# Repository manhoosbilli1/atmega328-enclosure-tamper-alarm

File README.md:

# Alarming_AC_Enclosure

ATmega328-based AC enclosure tamper/intrusion alarm with PowerPath, voltage monitoring, and dual switching converters

## At a Glance

- **Status**: In progress
- **Board size**: 100 x 60 mm
- **Layers**: 2
- **Components**: 98
- **Key ICs**:
  - U1: 74LVC1G00
  - U2: ATmega328-A
  - U3: LM5158QRTERQ1
  - U4: TPS62933DRLR
  - U5: LTC4412ES6#TRPBF
  - U6: LTC2960CTS8-1#TRMPBF

## Schematic

Full PDF: [reports/schematic.pdf](reports/schematic.pdf)

## Component Roles

- **ATmega328-A** - main MCU; reads tamper switches, manages alarm state, drives outputs
- **LTC4412ES6** - low-loss ideal-diode / PowerPath controller; manages source switching between mains-derived rail and backup battery seamlessly
- **LTC2960CTS8-1** - precision voltage monitor / supervisor; trips the alarm if either supply rail dips out of spec
- **LM5158QRTERQ1** - automotive-grade boost converter (LM5158-Q1); steps up battery voltage to feed the alarm load when on backup
- **TPS62933PDRLR** - low-Iq buck converter for the MCU rail (long battery standby)
- **DMN10H220L** - N-channel MOSFET for high-side / load switching
- **FDC610PZ** - P-channel MOSFET (complementary side for OR-ing / load isolation)
- **B220** - Schottky diode for reverse / OR-ing logic
- **BZT52Bxx** - zener diode for clamp / reference
- **1TS005F-2500-5001** - tactile reset/test switch
- **74LVC1G00** - single 2-input NAND gate for combining tamper inputs / debounce logic
- **Crystal** for ATmega clock

> Designed as a self-powered enclosure tamper alarm: stays armed on AC, falls back to battery when AC is cut, alerts when either supply rail is out of spec.

## PCB

**Top copper**

**Bottom copper**

## Bill of Materials

| Refs | Value | Footprint | Qty | MPN | LCSC |
|------|-------|-----------|----:|-----|------|
| C1,C5,C18 | 100nF | Capacitor_SMD:C_0603_1608Metric | 3 |  |  |
| C2,C3,C7,C17,C22,C25 | 100nF | Capacitor_SMD:C_0402_1005Metric | 6 |  |  |
| C4,C13,C14 | 4.7uF | Capacitor_SMD:C_0603_1608Metric | 3 |  |  |
| C6 | 22nF | Capacitor_SMD:C_0402_1005Metric | 1 |  |  |
| C8 | 10nF | Capacitor_SMD:C_0402_1005Metric | 1 |  |  |
| C9 | 1uF | Capacitor_SMD:C_0402_1005Metric | 1 |  |  |
| C10 | 100pF | Capacitor_SMD:C_0402_1005Metric | 1 |  |  |
| C11,C12 | 22pF | Capacitor_SMD:C_0402_1005Metric | 2 |  |  |
| C15,C16 | 10uF/50V | Capacitor_SMD:C_0805_2012Metric | 2 |  |  |
| C19,C20,C26 | 100uF/35V | Capacitor_SMD:CP_Elec_6.3x7.7 | 3 |  |  |
| C21 | 33nF | Capacitor_SMD:C_0402_1005Metric | 1 |  |  |
| C23,C24 | 22uF/35v | Capacitor_SMD:C_0805_2012Metric | 2 |  |  |
| D1 | B220 | Diode_SMD:D_SMB | 1 |  |  |
| D2 | BZT52B2V4 | Diode_SMD:D_SOD-123F | 1 |  |  |
| D3 | RED | LED_SMD:LED_0603_1608Metric | 1 |  |  |
| J1 | AVR-ISP-6 | Connector_PinSocket_2.54mm:PinSocket_2x03_P2.54mm_Vertical | 1 |  |  |
| J2 | Conn_01x04 | TerminalBlock_Phoenix:TerminalBlock_Phoenix_PT-1,5-4-3.5-H_1x04_P3.50mm_Horizontal | 1 |  |  |
| J3 | Conn_01x03 | TerminalBlock_Phoenix:TerminalBlock_Phoenix_PT-1,5-3-3.5-H_1x03_P3.50mm_Horizontal | 1 |  |  |
| J4 | BATTERY IN | TerminalBlock_Phoenix:TerminalBlock_Phoenix_PT-1,5-2-3.5-H_1x02_P3.50mm_Horizontal | 1 |  |  |
| J5 | WALL IN | TerminalBlock_Phoenix:TerminalBlock_Phoenix_PT-1,5-2-3.5-H_1x02_P3.50mm_Horizontal | 1 |  |  |
| L1 | 1.5uH | Inductor_SMD:L_Sunlord_MWSA0603S | 1 |  |  |
| L2 | 6.8uH | Inductor_SMD:L_TDK_SLF10165 | 1 |  |  |
| Q1-Q3 | DMN10H220L | Package_TO_SOT_SMD:SOT-23 | 3 |  |  |
| Q4,Q6 | FDC610PZ | FDC610PZ:SOT-23-6_L2.9-W1.6-P0.95-LS2.8-BR | 2 |  |  |
| Q5,Q7 | SI4435DY | SI4435DY:SOP-8_L4.9-W3.9-P1.27-LS6.0-BL | 2 |  |  |
| R1,R10-R14,R17 | 10K | Resistor_SMD:R_0603_1608Metric | 7 |  |  |
| R2 | 9.09K | Resistor_SMD:R_0402_1005Metric | 1 |  |  |
| R3 | 2.61K | Resistor_SMD:R_0402_1005Metric | 1 |  |  |
| R4,R20 | 1M | Resistor_SMD:R_0603_1608Metric | 2 |  |  |
| R5 | 49.9K 1% | Resistor_SMD:R_0402_1005Metric | 1 |  |  |
| R6 | 2.15K 1% | Resistor_SMD:R_0402_1005Metric | 1 |  |  |
| R7-R9 | 100R | Resistor_SMD:R_0603_1608Metric | 3 |  |  |
| R15 | 3M | Resistor_SMD:R_0603_1608Metric | 1 |  |  |
| R16 | 82K | Resistor_SMD:R_0603_1608Metric | 1 |  |  |
| R18 | 10.2K 1% | Resistor_SMD:R_0402_1005Metric | 1 |  |  |
| R19 | 53.6k 1% | Resistor_SMD:R_0402_1005Metric | 1 |  |  |
| R21,R22,R27 | 100K | Resistor_SMD:R_0603_1608Metric | 3 |  |  |
| R23 | 49.9R 1% | Resistor_SMD:R_0402_1005Metric | 1 |  |  |
| R24 | 4.7K | Resistor_SMD:R_0603_1608Metric | 1 |  |  |
| R25 | 4.3K | Resistor_SMD:R_0603_1608Metric | 1 |  |  |
| R26 | 510K | Resistor_SMD:R_0603_1608Metric | 1 |  |  |
| R28 | 5.6M | Resistor_SMD:R_0603_1608Metric | 1 |  |  |
| RV1,RV2 | 10K | Potentiometer_SMD:Potentiometer_Bourns_3314J_Vertical | 2 |  |  |
| SW1 | 1TS005F-2500-5001 | 1TS005F-2500-5001:SW-SMD_4P-L6.0-W6.0-P4.50-LS9.0-H2.5 | 1 |  |  |
| SW2,SW3 | SW_Push | TerminalBlock_Phoenix:TerminalBlock_Phoenix_PT-1,5-2-3.5-H_1x02_P3.50mm_Horizontal | 2 |  |  |
| TP1,TP2 | TestPoint | TestPoint:TestPoint_Pad_D1.5mm | 2 |  |  |
| U1 | 74LVC1G00 | Package_TO_SOT_SMD:SOT-23-5 | 1 |  |  |
| U2 | ATmega328-A | Package_QFP:TQFP-32_7x7mm_P0.8mm | 1 |  |  |
| U3 | LM5158QRTERQ1 | Package_DFN_QFN:WQFN-16-1EP_3x3mm_P0.5mm_EP1.68x1.68mm | 1 |  |  |
| U4 | TPS62933DRLR | Package_TO_SOT_SMD:SOT-583-8 | 1 |  |  |
| U5 | LTC4412ES6#TRPBF | LTC4412ES6#TRPBF:TSOT-23-6_L2.9-W1.6-P0.95-LS2.8-BR | 1 |  |  |
| U6 | LTC2960CTS8-1#TRMPBF | LTC2960CTS8-1#TRMPBF:TSOT-23-8_L2.9-W1.6-P0.65-LS2.8-BL | 1 |  |  |
| Y1 | 16MHZ | Crystal:Crystal_SMD_5032-2Pin_5.0x3.2mm | 1 |  |  |

_53 of 53 line items don't have an LCSC code in the schematic - search [LCSC](https://www.lcsc.com/) or [JLC parts search](https://jlcsearch.tscircuit.com/) by MPN or footprint when sourcing._

## Files

- `Alarming_AC_Enclosure.kicad_pro` - KiCad project
- `Alarming_AC_Enclosure.kicad_sch` - schematic source
- `Alarming_AC_Enclosure.kicad_pcb` - PCB layout source
- `reports/schematic.pdf` - full schematic (printable)
- `reports/bom.csv` - bill of materials
- `reports/pcb-top.svg`, `reports/pcb-bottom.svg` - copper artwork
- `reports/board-stats.json` - KiCad-generated board statistics

---

_Renders and metadata auto-generated by `Backup-KiCadProject.ps1` using KiCad 10.0._

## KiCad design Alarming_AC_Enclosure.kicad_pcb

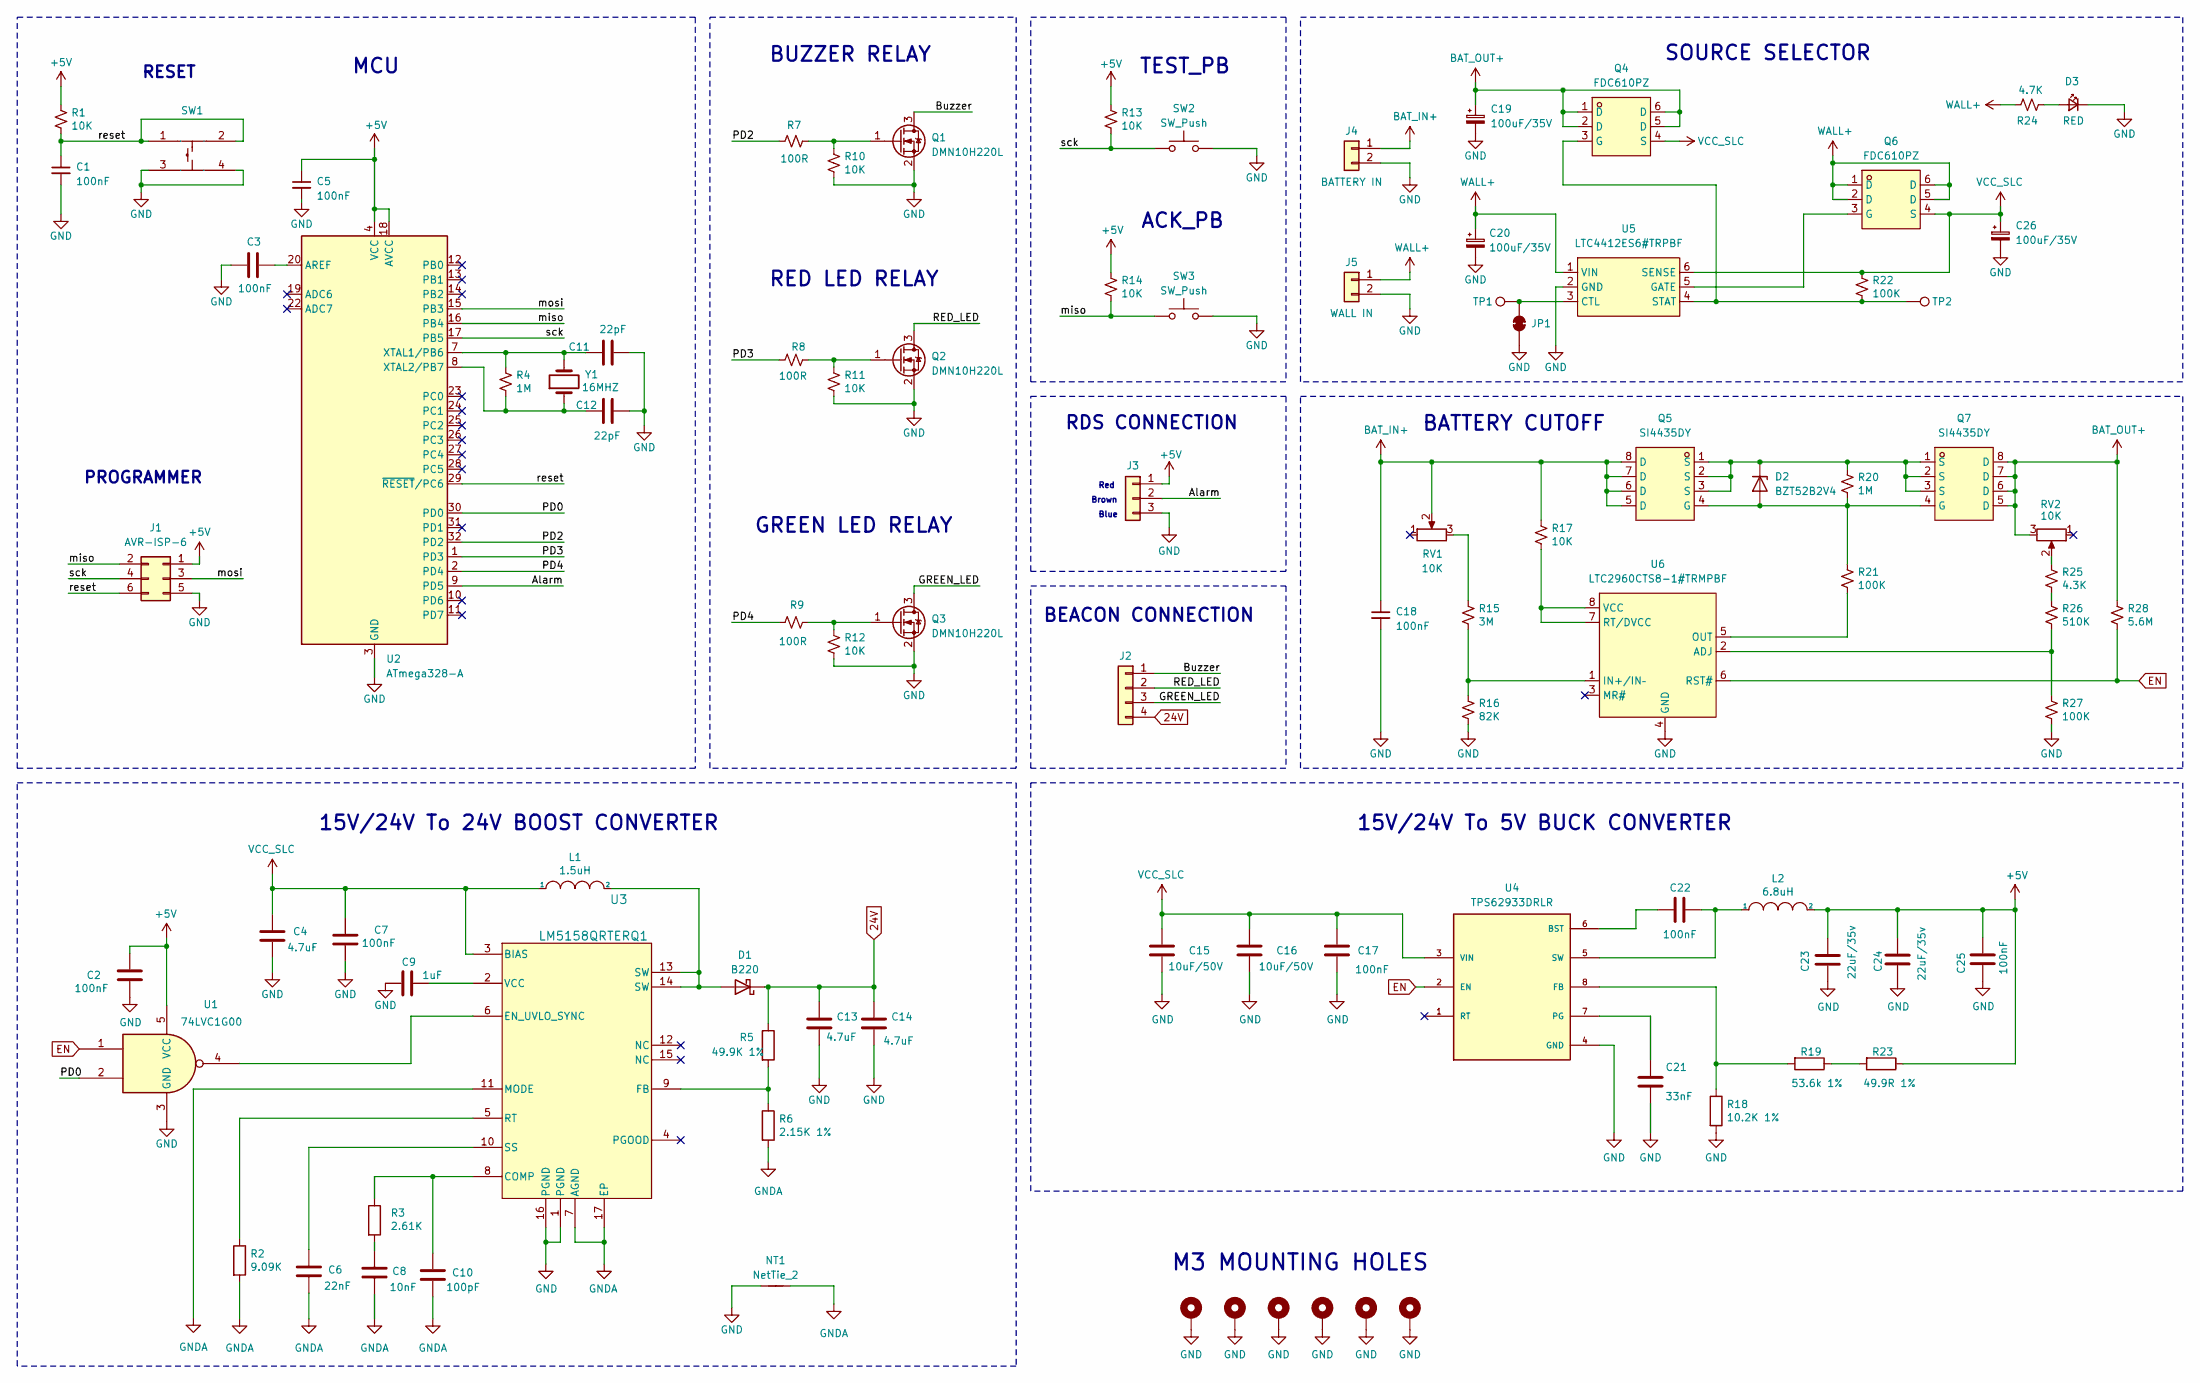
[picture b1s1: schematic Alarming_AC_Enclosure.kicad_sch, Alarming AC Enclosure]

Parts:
C1, C5, C18: 100nF; C_0603_1608Metric; JLCPCB Part # C14663
C2, C3, C7, C17, C22, C25: 100nF; C_0402_1005Metric; JLCPCB Part # C307331
C4, C13, C14: 4.7uF; C_0603_1608Metric; JLCPCB Part # C69335
C6: 22nF; C_0402_1005Metric; JLCPCB Part # C1532
C8: 10nF; C_0402_1005Metric; JLCPCB Part # C15195
C9: 1uF; C_0402_1005Metric; JLCPCB Part # C52923
C10: 100pF; C_0402_1005Metric; JLCPCB Part # C1546
C11, C12: 22pF; C_0402_1005Metric; JLCPCB Part # C1555
C15, C16: 10uF/50V; C_0805_2012Metric; JLCPCB Part # C440198
C19, C20, C26: 100uF/35V; CP_Elec_6.3x7.7; JLCPCB Part # C3339
C21: 33nF; C_0402_1005Metric; JLCPCB Part # C106862
C23, C24: 22uF/35v; C_0805_2012Metric; JLCPCB Part # C338080
D1: B220; D_SMB; JLCPCB Part # C110480
D2: BZT52B2V4; D_SOD-123F; JLCPCB Part # C3019930
D3: RED; LED_0603_1608Metric; JLCPCB Part # C2286
H1, H2, H3, H4, H5, H6: MountingHole; MountingHole_3.2mm_M3_DIN965_Pad
J1: AVR-ISP-6; PinSocket_2x03_P2.54mm_Vertical; JLCPCB Part # C7501274
J2: Conn_01x04; TerminalBlock_Phoenix_PT-1,5-4-3.5-H_1x04_P3.50mm_Horizontal; JLCPCB Part # C2757925
J3: Conn_01x03; TerminalBlock_Phoenix_PT-1,5-3-3.5-H_1x03_P3.50mm_Horizontal; JLCPCB Part # C466971
J4: BATTERY IN; TerminalBlock_Phoenix_PT-1,5-2-3.5-H_1x02_P3.50mm_Horizontal; JLCPCB Part # C415432
J5: WALL IN; TerminalBlock_Phoenix_PT-1,5-2-3.5-H_1x02_P3.50mm_Horizontal; JLCPCB Part # C415432
JP1: SolderJumper_2_Bridged; SolderJumper-2_P1.3mm_Bridged_RoundedPad1.0x1.5mm
L1: 1.5uH; L_Sunlord_MWSA0603S; JLCPCB Part # C167217
L2: 6.8uH; L_TDK_SLF10165; JLCPCB Part # C138669
NT1: NetTie_2; NetTie-2_SMD_Pad2.0mm
Q1, Q2, Q3: DMN10H220L; SOT-23; JLCPCB Part # C5122013
Q4, Q6: FDC610PZ; SOT-23-6_L2.9-W1.6-P0.95-LS2.8-BR; JLCPCB Part # C241761
Q5, Q7: SI4435DY; SOP-8_L4.9-W3.9-P1.27-LS6.0-BL; JLCPCB Part # C4355022
R1, R10, R11, R12, R13, R14, R17: 10K; R_0603_1608Metric; JLCPCB Part # C25804
R2: 9.09K; R_0402_1005Metric; JLCPCB Part # C11549
R3: 2.61K; R_0402_1005Metric; JLCPCB Part # C34906
R4, R20: 1M; R_0603_1608Metric; JLCPCB Part # C22935
R5: 49.9K 1%; R_0402_1005Metric; JLCPCB Part # C25897
R6: 2.15K 1%; R_0402_1005Metric; JLCPCB Part # C25878
R7, R8, R9: 100R; R_0603_1608Metric; JLCPCB Part # C22775
R15: 3M; R_0603_1608Metric; JLCPCB Part # C23156
R16: 82K; R_0603_1608Metric; JLCPCB Part # C23254
R18: 10.2K 1%; R_0402_1005Metric; JLCPCB Part # C11660
R19: 53.6k 1%; R_0402_1005Metric; JLCPCB Part # C53398
R21, R22, R27: 100K; R_0603_1608Metric; JLCPCB Part # C25803
R23: 49.9R 1%; R_0402_1005Metric; JLCPCB Part # C25120
R24: 4.7K; R_0603_1608Metric; JLCPCB Part # C23162
R25: 4.3K; R_0603_1608Metric; JLCPCB Part # C23159
R26: 510K; R_0603_1608Metric; JLCPCB Part # C23192
R28: 5.6M; R_0603_1608Metric; JLCPCB Part # C23190
RV1, RV2: 10K; Potentiometer_Bourns_3314J_Vertical; JLCPCB Part # C36376
SW1: 1TS005F-2500-5001; SW-SMD_4P-L6.0-W6.0-P4.50-LS9.0-H2.5; JLCPCB Part # C255812
SW2, SW3: SW_Push; TerminalBlock_Phoenix_PT-1,5-2-3.5-H_1x02_P3.50mm_Horizontal; JLCPCB Part # C415432
TP1, TP2: TestPoint; TestPoint_Pad_D1.5mm
U1: 74LVC1G00; SOT-23-5; JLCPCB Part # C434066
U2: ATmega328-A; TQFP-32_7x7mm_P0.8mm; JLCPCB Part # C14877
U3: LM5158QRTERQ1; WQFN-16-1EP_3x3mm_P0.5mm_EP1.68x1.68mm; JLCPCB Part # C3188431
U4: TPS62933DRLR; SOT-583-8; JLCPCB Part # C3200405
U5: LTC4412ES6#TRPBF; TSOT-23-6_L2.9-W1.6-P0.95-LS2.8-BR; JLCPCB Part # C514442
U6: LTC2960CTS8-1#TRMPBF; TSOT-23-8_L2.9-W1.6-P0.65-LS2.8-BL; JLCPCB Part # C683822
Y1: 16MHZ; Crystal_SMD_5032-2Pin_5.0x3.2mm; JLCPCB Part # C251590

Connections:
24V: C13.1, C14.1, D1.1 (K), J2.4, R5.1; also elsewhere on the board
+5V: C2.2, C5.1, C23.1, C24.1, C25.2, J1.1, J3.1, L2.2, R1.1, R13.1, R14.1, R23.1, U1.5 (VCC), U2.4 (VCC), U2.6 (VCC), U2.18 (AVCC); also elsewhere on the board
/Alarm: J3.2, U2.9 (PD5)
/Buzzer: J2.1, Q1.3 (D)
/GREEN_LED: J2.3, Q3.3 (D)
/PD0: U1.2, U2.30 (PD0)
/PD2: R7.1, U2.32 (PD2)
/PD3: R8.1, U2.1 (PD3)
/PD4: R9.1, U2.2 (PD4)
/RED_LED: J2.2, Q2.3 (D)
/miso: J1.2, R14.2, SW3.1, U2.16 (PB4)
/mosi: J1.3, U2.15 (PB3)
/reset: C1.1, J1.6, R1.2, SW1.1, SW1.2, U2.29 (~RESET/PC6)
/sck: J1.4, R13.2, SW2.1, U2.17 (PB5)
BAT_IN+: C18.1, J4.1, Q5.5 (D), Q5.6 (D), Q5.7 (D), Q5.8 (D), R17.1, RV1.2
BAT_OUT+: C19.1, Q4.1 (D), Q4.2 (D), Q4.5 (D), Q4.6 (D), Q7.5 (D), Q7.6 (D), Q7.7 (D), Q7.8 (D), R28.1, RV2.3
EN: R28.2, U1.1, U4.2 (EN), U6.6 (RST#)
GND: C1.2, C2.1, C3.2, C4.2, C5.2, C7.1, C9.1, C11.2, C12.2, C13.2, C14.2, C15.2, C16.2, C17.1, C18.2, C19.2, C20.2, C21.2, C23.2, C24.2, C25.1, C26.2, D3.1 (K), H1.1, H2.1, H3.1, H4.1, H5.1, H6.1, J1.5, J3.3, J4.2, J5.2, JP1.1 (A), NT1.1, Q1.2 (S), Q2.2 (S), Q3.2 (S), R10.2, R11.2, R12.2, R16.2, R18.2, R27.2, SW1.3, SW1.4, SW2.2, SW3.2, U1.3 (GND), U2.3 (GND), U2.5 (GND), U2.21 (GND), U3.1 (PGND), U3.16 (PGND), U4.4 (GND), U5.2 (GND), U6.4 (GND); also elsewhere on the board
GNDA: C6.2, C8.2, C10.2, NT1.2, R2.2, R6.2, U3.7 (AGND), U3.11 (MODE), U3.17 (EP)
unnamed: C8.1, R3.2
unnamed: D1.2 (A), L1.2, U3.13 (SW), U3.14 (SW)
unnamed: D2.2 (A), Q5.4 (G), Q7.4 (G), R20.2, R21.1
unnamed: D2.1 (K), Q5.1 (S), Q5.2 (S), Q5.3 (S), Q7.1 (S), Q7.2 (S), Q7.3 (S), R20.1
unnamed: D3.2 (A), R24.2
unnamed: JP1.2 (B), TP1.1, U5.3 (CTL)
unnamed: Q1.1 (G), R7.2, R10.1
unnamed: Q2.1 (G), R8.2, R11.1
unnamed: Q3.1 (G), R9.2, R12.1
unnamed: Q4.3 (G), R22.2, TP2.1, U5.4 (STAT)
unnamed: Q6.3 (G), U5.5 (GATE)
unnamed: R15.1, RV1.3
unnamed: R19.1, R23.2
unnamed: R25.1, RV2.2
unnamed: R25.2, R26.1
unnamed: C3.1, U2.20 (AREF)
unnamed: C11.1, R4.1, U2.7 (XTAL1/PB6), Y1.2
unnamed: C12.1, R4.2, U2.8 (XTAL2/PB7), Y1.1
unnamed: C10.1, R3.1, U3.8 (COMP)
unnamed: U1.4, U3.6 (EN_UVLO_SYNC)
unnamed: R5.2, R6.1, U3.9 (FB)
unnamed: R2.1, U3.5 (RT)
unnamed: C6.1, U3.10 (SS)
unnamed: C9.2, U3.2 (VCC)
unnamed: C22.1, U4.6 (BST)
unnamed: R18.1, R19.2, U4.8 (FB)
unnamed: C21.1, U4.7 (PG)
unnamed: C22.2, L2.1, U4.5 (SW)
unnamed: R26.2, R27.1, U6.2 (ADJ)
unnamed: R15.2, R16.1, U6.1 (IN+/IN–)
unnamed: R21.2, U6.5 (OUT)
unnamed: R17.2, U6.7 (RT/DVCC), U6.8 (VCC)
VCC_SLC: C4.1, C7.2, C15.1, C16.1, C17.2, C26.1, L1.1, Q4.4 (S), Q6.4 (S), R22.1, U3.3 (BIAS), U4.3 (VIN), U5.6 (SENSE)
WALL+: C20.1, J5.1, Q6.1 (D), Q6.2 (D), Q6.5 (D), Q6.6 (D), R24.1, U5.1 (VIN)

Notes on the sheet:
Red
Blue
15V/24V To 24V BOOST CONVERTER
RED LED RELAY
TEST_PB
15V/24V To 5V BUCK CONVERTER
RDS CONNECTION
ACK_PB
Brown
RESET
BATTERY CUTOFF
MCU
SOURCE SELECTOR
M3 MOUNTING HOLES
BEACON CONNECTION
PROGRAMMER
BUZZER RELAY
GREEN LED RELAY

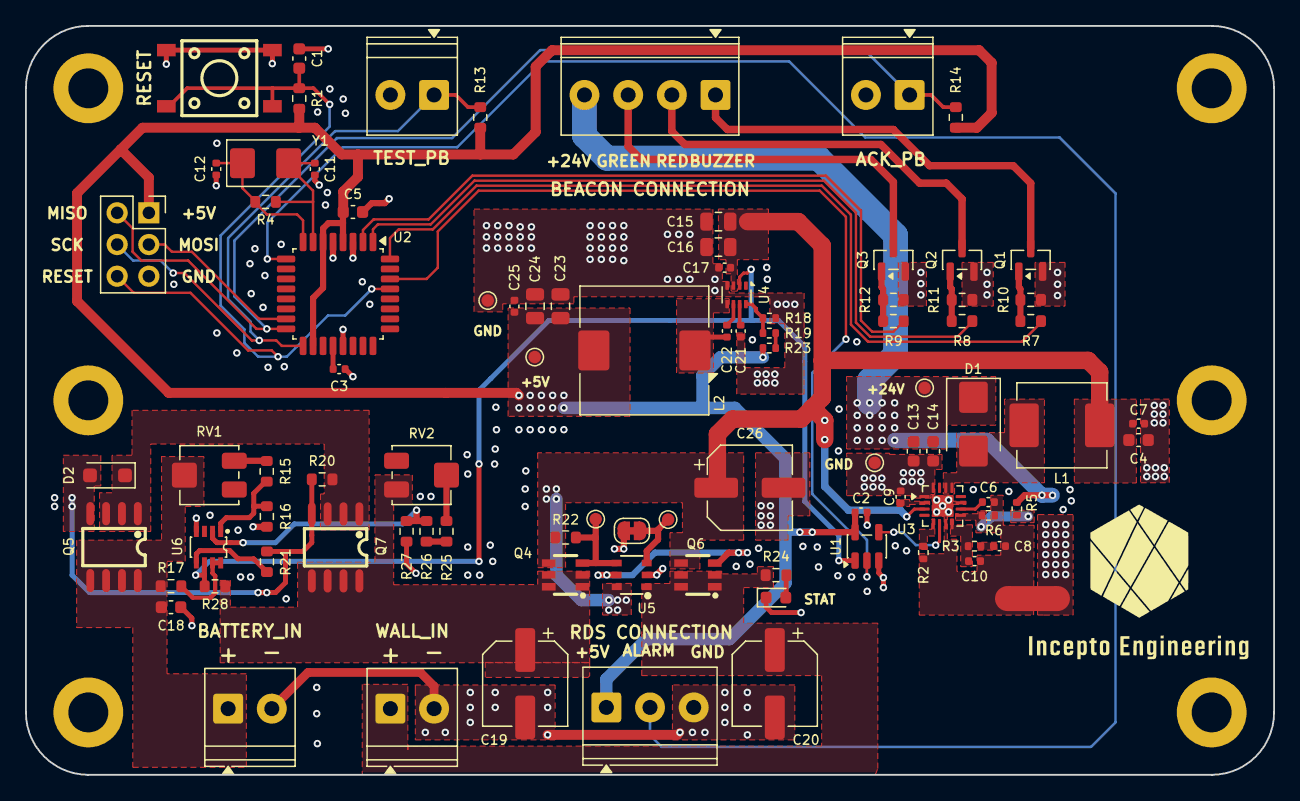
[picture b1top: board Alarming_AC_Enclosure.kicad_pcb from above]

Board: 2 copper layers, 100.0 x 60.0 mm, 97 parts (0 on the bottom side), 53 nets.

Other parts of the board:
TP3, TP4, TP5, TP6: TestPoint; TestPoint_Pad_D1.0mm

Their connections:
24V: TP3.1; also elsewhere on the board
+5V: TP5.1; also elsewhere on the board
GND: TP4.1, TP6.1; also elsewhere on the board

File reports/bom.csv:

"Refs","Value","Footprint","Qty","Description","Mfr","MPN","LCSC"
"C1,C5,C18","100nF","Capacitor_SMD:C_0603_1608Metric","3","","","",""
"C2,C3,C7,C17,C22,C25","100nF","Capacitor_SMD:C_0402_1005Metric","6","","","",""
"C4,C13,C14","4.7uF","Capacitor_SMD:C_0603_1608Metric","3","","","",""
"C6","22nF","Capacitor_SMD:C_0402_1005Metric","1","","","",""
"C8","10nF","Capacitor_SMD:C_0402_1005Metric","1","","","",""
"C9","1uF","Capacitor_SMD:C_0402_1005Metric","1","","","",""
"C10","100pF","Capacitor_SMD:C_0402_1005Metric","1","","","",""
"C11,C12","22pF","Capacitor_SMD:C_0402_1005Metric","2","","","",""
"C15,C16","10uF/50V","Capacitor_SMD:C_0805_2012Metric","2","","","",""
"C19,C20,C26","100uF/35V","Capacitor_SMD:CP_Elec_6.3x7.7","3","-55℃~+105℃ 100uF 2000hrs@105℃ 35V 6.3mm 7.7mm ±20% SMD,D6.3xL7.7mm Aluminum Electrolytic Capacitors - SMD ROHS","","",""
"C21","33nF","Capacitor_SMD:C_0402_1005Metric","1","","","",""
"C23,C24","22uF/35v","Capacitor_SMD:C_0805_2012Metric","2","","","",""
"D1","B220","Diode_SMD:D_SMB","1","","","",""
"D2","BZT52B2V4","Diode_SMD:D_SOD-123F","1","500mW Zener Diode, SOD-123F","","",""
"D3","RED","LED_SMD:LED_0603_1608Metric","1","-40℃~+85℃ 120° 2.4V 20mA 300mcd 40mW 615nm~630nm 645nm Red Water Clear 0603 LED Indication - Discrete ROHS","","",""
"J1","AVR-ISP-6","Connector_PinSocket_2.54mm:PinSocket_2x03_P2.54mm_Vertical","1","Generic connector, double row, 02x03, odd/even pin numbering scheme (row 1 odd numbers, row 2 even numbers), script generated (kicad-library-utils/schlib/autogen/connector/)","","",""
"J2","Conn_01x04","TerminalBlock_Phoenix:TerminalBlock_Phoenix_PT-1,5-4-3.5-H_1x04_P3.50mm_Horizontal","1","","","",""
"J3","Conn_01x03","TerminalBlock_Phoenix:TerminalBlock_Phoenix_PT-1,5-3-3.5-H_1x03_P3.50mm_Horizontal","1","","","",""
"J4","BATTERY IN","TerminalBlock_Phoenix:TerminalBlock_Phoenix_PT-1,5-2-3.5-H_1x02_P3.50mm_Horizontal","1","-40℃~+105℃ 0.5~1.5 1 10A 150V 16~26 1x2P 2 2P 3.5mm Green M2 Through Hole Plugin,P=3.5mm Screw Terminal Blocks ROHS","","",""
"J5","WALL IN","TerminalBlock_Phoenix:TerminalBlock_Phoenix_PT-1,5-2-3.5-H_1x02_P3.50mm_Horizontal","1","-40℃~+105℃ 0.5~1.5 1 10A 150V 16~26 1x2P 2 2P 3.5mm Green M2 Through Hole Plugin,P=3.5mm Screw Terminal Blocks ROHS","","",""
"L1","1.5uH","Inductor_SMD:L_Sunlord_MWSA0603S","1","","","",""
"L2","6.8uH","Inductor_SMD:L_TDK_SLF10165","1","","","",""
"Q1-Q3","DMN10H220L","Package_TO_SOT_SMD:SOT-23","3","","","",""
"Q4,Q6","FDC610PZ","FDC610PZ:SOT-23-6_L2.9-W1.6-P0.95-LS2.8-BR","2","-55℃~+150℃ 1 P-Channel 1.005nF 1.6W 190pF 195pF 24nC@10V 30V 3V@250uA 4.9A 75mΩ@4.5V P-Channel SuperSOT-6 MOSFETs ROHS","","",""
"Q5,Q7","SI4435DY","SI4435DY:SOP-8_L4.9-W3.9-P1.27-LS6.0-BL","2","-55℃~+150℃ 1.2nF@15V 12A 150pF 1V 25nC 30V 3W 9.5mΩ@10V SOP-8 MOSFETs ROHS","","",""
"R1,R10-R14,R17","10K","Resistor_SMD:R_0603_1608Metric","7","","","",""
"R2","9.09K","Resistor_SMD:R_0402_1005Metric","1","","","",""
"R3","2.61K","Resistor_SMD:R_0402_1005Metric","1","","","",""
"R4,R20","1M","Resistor_SMD:R_0603_1608Metric","2","","","",""
"R5","49.9K 1%","Resistor_SMD:R_0402_1005Metric","1","","","",""
"R6","2.15K 1%","Resistor_SMD:R_0402_1005Metric","1","","","",""
"R7-R9","100R","Resistor_SMD:R_0603_1608Metric","3","","","",""
"R15","3M","Resistor_SMD:R_0603_1608Metric","1","","","",""
"R16","82K","Resistor_SMD:R_0603_1608Metric","1","","","",""
"R18","10.2K 1%","Resistor_SMD:R_0402_1005Metric","1","","","",""
"R19","53.6k 1%","Resistor_SMD:R_0402_1005Metric","1","","","",""
"R21,R22,R27","100K","Resistor_SMD:R_0603_1608Metric","3","","","",""
"R23","49.9R 1%","Resistor_SMD:R_0402_1005Metric","1","","","",""
"R24","4.7K","Resistor_SMD:R_0603_1608Metric","1","","","",""
"R25","4.3K","Resistor_SMD:R_0603_1608Metric","1","","","",""
"R26","510K","Resistor_SMD:R_0603_1608Metric","1","","","",""
"R28","5.6M","Resistor_SMD:R_0603_1608Metric","1","","","",""
"RV1,RV2","10K","Potentiometer_SMD:Potentiometer_Bourns_3314J_Vertical","2","1 10kΩ 250mW ±100ppm/℃ ±20% SMD,4.5x4.5mm Potentiometers, Variable Resistors ROHS","","",""
"SW1","1TS005F-2500-5001","1TS005F-2500-5001:SW-SMD_4P-L6.0-W6.0-P4.50-LS9.0-H2.5","1","Circuit:SPST Actuator Style:Round Button Operating Force:2.5N Mounting Type:Surface Mount,Vertical Length:6mm Width:6mm Switch Height:5mm with Bracket:Without Bracket Contact Current:50mA Voltage Rating:12V Actuator/Cap Color:Black With Lamp:No Terminatio","","",""
"SW2,SW3","SW_Push","TerminalBlock_Phoenix:TerminalBlock_Phoenix_PT-1,5-2-3.5-H_1x02_P3.50mm_Horizontal","2","","","",""
"TP1,TP2","TestPoint","TestPoint:TestPoint_Pad_D1.5mm","2","test point","","",""
"U1","74LVC1G00","Package_TO_SOT_SMD:SOT-23-5","1","","","",""
"U2","ATmega328-A","Package_QFP:TQFP-32_7x7mm_P0.8mm","1","","","",""
"U3","LM5158QRTERQ1","Package_DFN_QFN:WQFN-16-1EP_3x3mm_P0.5mm_EP1.68x1.68mm","1","","","",""
"U4","TPS62933DRLR","Package_TO_SOT_SMD:SOT-583-8","1","-40℃~+150℃@(TJ) 1 12uA 2.2MHz 3.8V~30V 3A 800mV~22V Adjustable Buck Buck Built-In Yes SOT-583 DC-DC Converters ROHS","","",""
"U5","LTC4412ES6#TRPBF","LTC4412ES6#TRPBF:TSOT-23-6_L2.9-W1.6-P0.95-LS2.8-BR","1","-40℃~+85℃ 1 110us 11uA 13us 2.5V~28V 350mV 635mV MOSFET TSOT-23-6 Gate Drivers ROHS","","",""
"U6","LTC2960CTS8-1#TRMPBF","LTC2960CTS8-1#TRMPBF:TSOT-23-8_L2.9-W1.6-P0.65-LS2.8-BL","1","0℃~+70℃@(Tj) 15ms 2 2.5V~36V 400mV 850nA Active Low Open Drain Voltage Monitor Yes TSOT-23-8 Supervisor and Reset ICs ROHS","","",""
"Y1","16MHZ","Crystal:Crystal_SMD_5032-2Pin_5.0x3.2mm","1","","","",""

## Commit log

2026-05-18 Initial backup: schematic, PCB, renders, BOM
2026-05-18 Enrich README: schematic PNG, component roles, BOM table
